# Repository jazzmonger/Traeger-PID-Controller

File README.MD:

*4/15/25 - NOTE: project has been upgrade to an ESP32S3. Touch and display are just too much for the little D1. S3 handles it no problem.  New design files now uploaded to rev 2.2.0*

This project is for a generic ESP32 Based Traeger Pellet Smoker/Grill controller that can be used on any smoker/grill that has an auger, hotrod and fan used for control. Full Home Assistant control completes it and the sky is the limit on what can be done with it using automations.  See my ESPHome Forums post for discussions https://community.home-assistant.io/t/generic-traeger-smoker-grill-controller/867494

The inspiration for much of this project came from the excellent work done be @Nebhead and the PiSmoker project (https://github.com/nebhead/PiFire) based on the Raspberry Pi. Their Discord channel is here https://discord.com/channels/1027346882156052550/1027348991135985796

While I respect the platform for what it is, I'm not a huge Raspberry Pi fan and I wanted something based on an ESP32 and ESPHome that would integrate seamlessly into Home Assistant. So, this project was born.

Some key attributes of this scaled down version:

* its written in ESPHome, so its easy to understand and modify
* It can be used standalone or with Home Assistant
* it integrates seamlessly with Home Assistant and all functions are controllable via a LoveLace dashboard both on a PC and in the Home Assistant app.
* it emulates the existing new Trager controllers in all functions and adds several new functions
* it controls 1 auger, 1 hotrod & 1 fan found on the vast majority of pellet smokers
* it uses solid state relays for control
* it uses the existing PT1000 temperature sensor (can be adapted to a PT100)
* it adds a Smith-Predicting, PID temperature compensating control
* it controls the chamber temperature within approximately +/- 5F vs the +/- 25F for existing controllers
* rotary encoder support so you can control your grill temp with a spinny knob
* it has an interactive, touch screen ili9341 display
* it adds 3 optional configurable wired meat probes
* it allows dynamic configuration of ALL paramaters so it is infinitly tuneable to any pellet smoker
* it also allows for both touch screen control of all functions as well as optional individual buttons for control.
* it adds an optional VL53L0X Time of Flight (TOF) Sensor sensor to measure hopper pellet levels
* Circuit board for this scaled down version is exactly the same size as the Traeger controller allowing easy retrofit installation.

Outstanding temperature control even when opening the lid of the smoker.  Very little overshoot when adjusting temperatures (Smith Predictor).
Fully adjustable PID Params (advanced)
Lovelace Dashboards with animated icons for fans, auger & hotrod

Full architecture doc here https://github.com/jazzmonger/Traeger-PID-Controller/blob/main/doc/1Traeger-S3-operation-summary.md

This is a work in progress. I'm not affilaiated with Traeger or any other BBQ or smoker company. The design may or may not work with your gril, so, your mileage may vary. The chip Im using in this design is an ESP32 D1 Mini. Its small size,wide availability, and versatility makes it ideal for this use. You can probably use any ESP32 based dev board, but I cannot guarantee it will work. My larger project uses an ESP32-S3 as I needed every single available GPIO on that chip, and then some. Plus I needed to use the ESP-IDF framework for that project and also needed PSRAM, hence the S3 based board choice.

This project has been a ton of fun.  It's a couple thousand lines of ESPHome code so it's not a "beginner" project by any definition.  But if you study the code long enough, you'll begin to make sense of it all - that's what I love about ESPHome. It's easily approachable by novice users. 

Also, because this controller offers the ability to completely customize literally everything, it will take time for you to realize its full potential.  The PID tuning is especially complex, but after many days of testing, I've settled on PID value parameters that do a reasonable job of keeping the chamber temps within +/- 5F or so,  a far cry from the +/-25F of the current controllers. Adding the Smith Predictor to the PID controller eliminates overshoots from wide temperature changes. Many kudos must go to @dogtreatfairy for many hours spent helping me tune the PID controller.

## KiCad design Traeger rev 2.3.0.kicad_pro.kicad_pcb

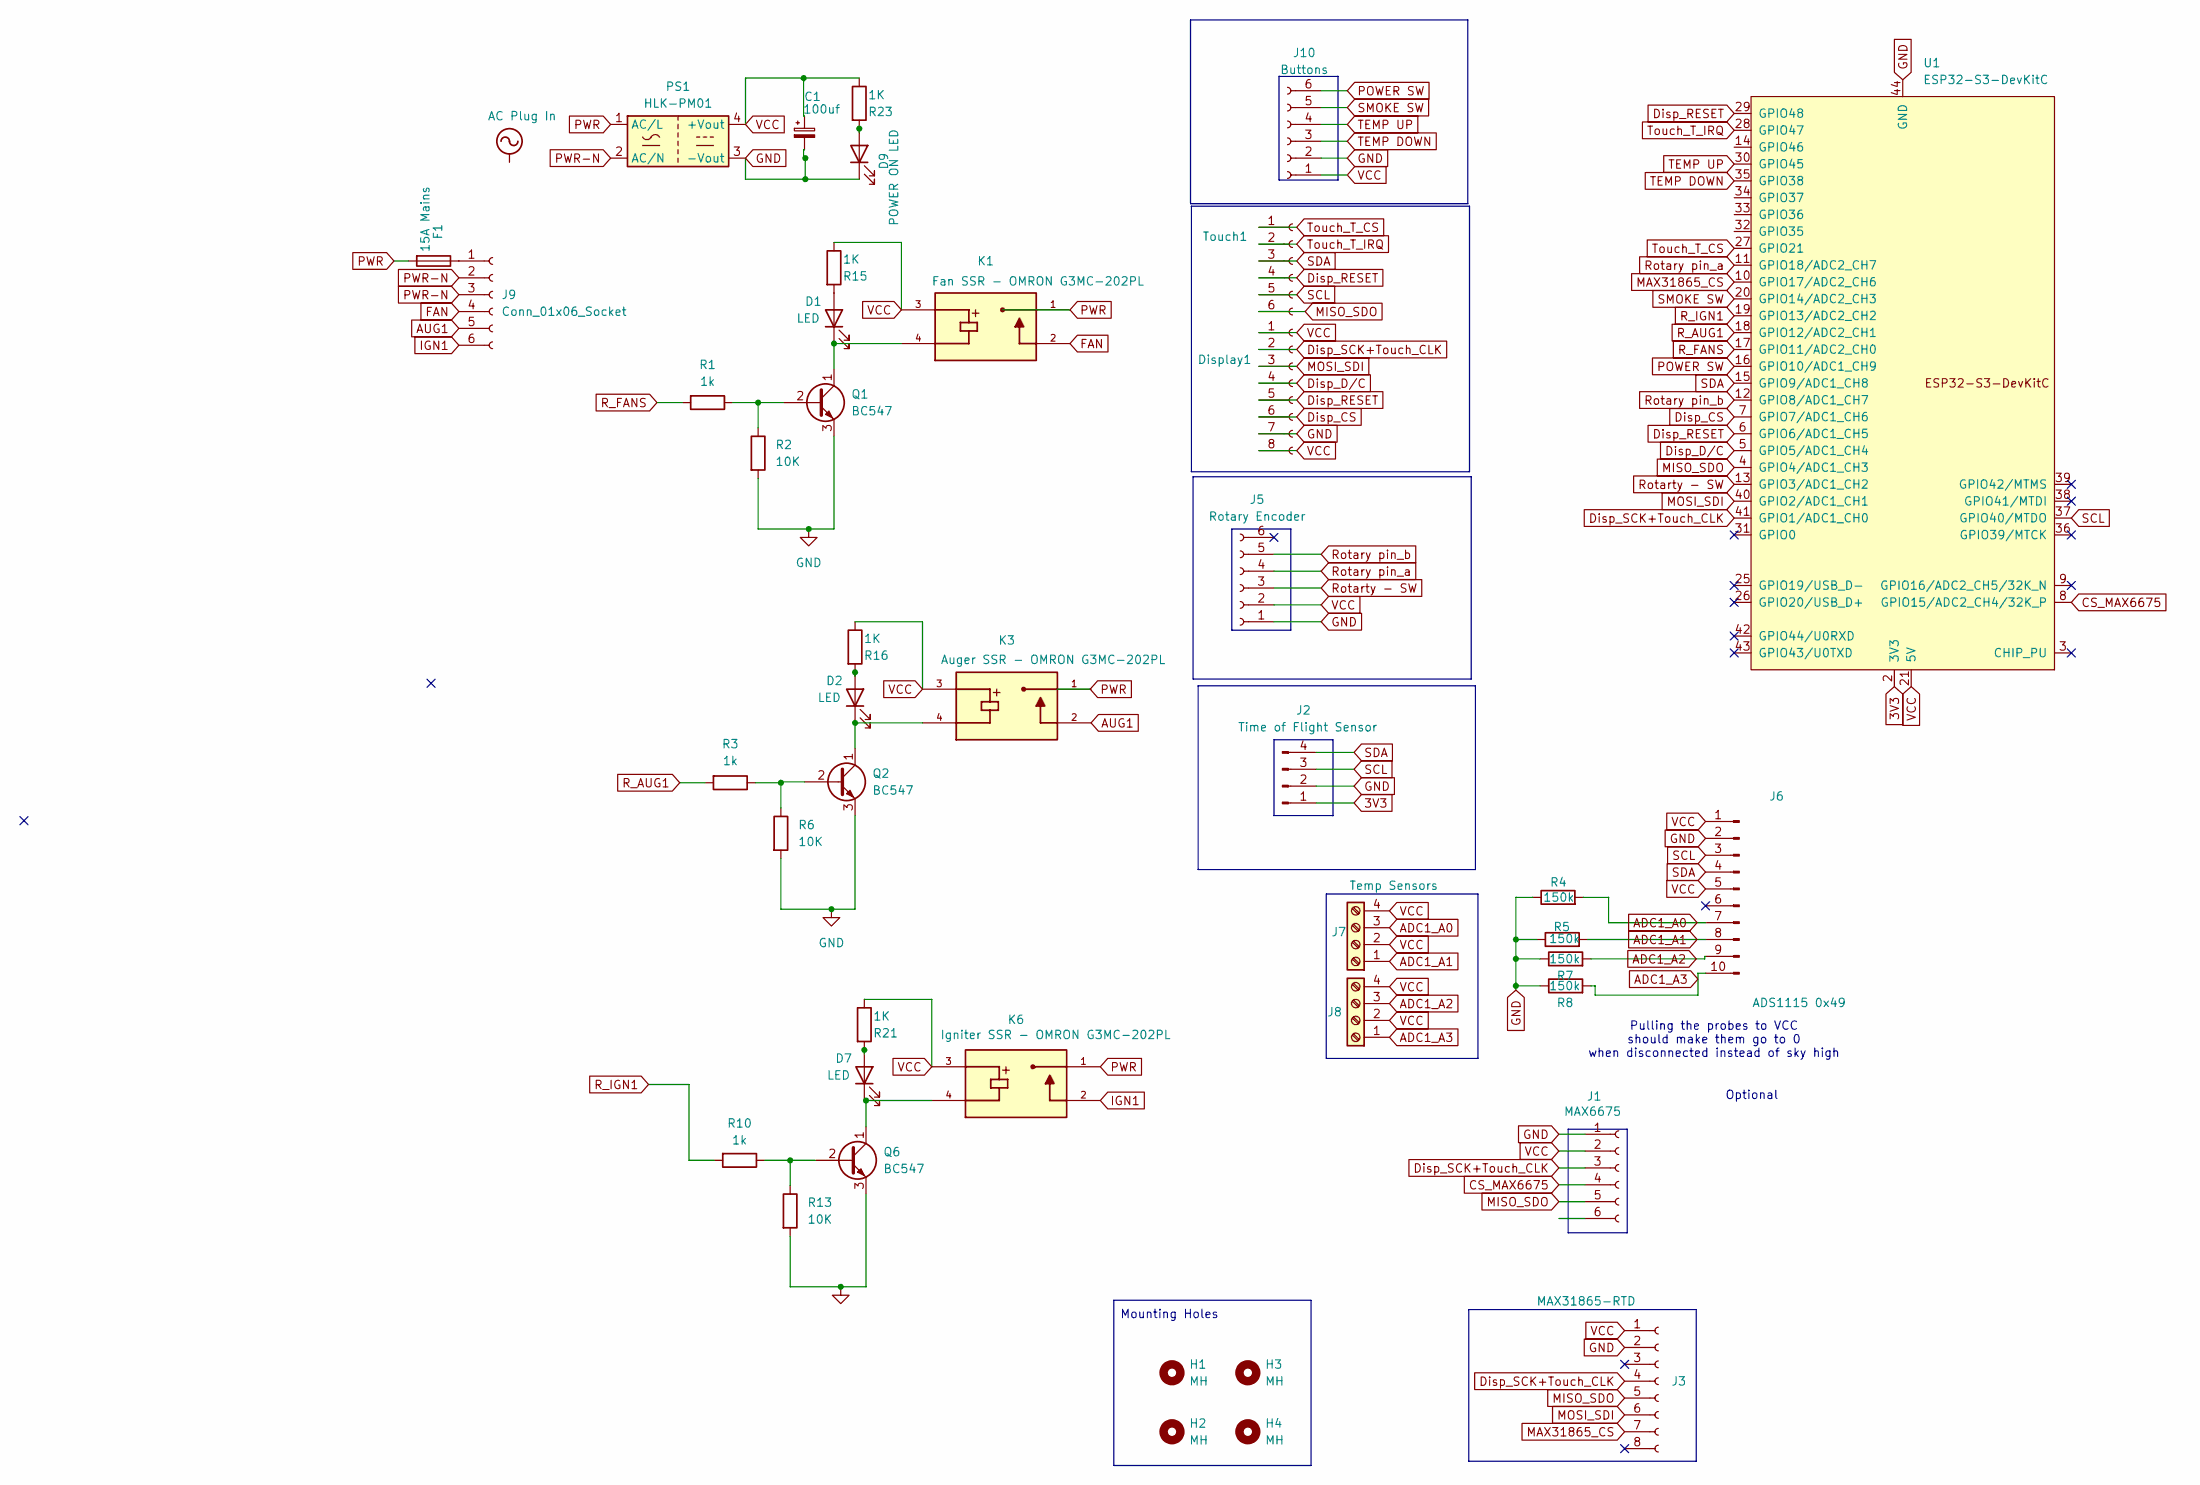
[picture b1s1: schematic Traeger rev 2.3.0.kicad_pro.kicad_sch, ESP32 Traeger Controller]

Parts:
C1: 100uf; CP_Radial_D8.0mm_P3.50mm
D1, D2, D7: LED; LED_D3.0mm
D9: POWER ON LED; LED_D3.0mm
Display1: Conn_01x08_Socket; JST_EH_B8B-EH-A_1x08_P2.50mm_Vertical
F1: 15A Mains; Fuse Block 3544-2_KEYSTONE
H1, H2, H3, H4: MH; MountingHole_3.2mm_M3
J1: MAX6675; JST_XH_B6B-XH-A_1x06_P2.50mm_Vertical
J2: Time of Flight Sensor; JST_EH_B4B-EH-A_1x04_P2.50mm_Vertical
J3: MAX31865-RTD; PinSocket_1x08_P2.54mm_Vertical
J5: Rotary Encoder; JST_XH_B6B-XH-A_1x06_P2.50mm_Vertical
J6: ADS1115 0x49; PinSocket_1x10_P2.54mm_Vertical
J7, J8: Temp Sensors; TerminalBlock_RND_205-00014_1x04_P5.00mm_Horizontal
J9: Conn_01x06_Socket; TerminalBlock_RND_205-00005_1x06_P5.00mm_Horizontal
J10: Buttons; JST_XH_B6B-XH-A_1x06_P2.50mm_Vertical
K1: Fan SSR - OMRON G3MC-202PL; RELAY_G3MB-202PDC5; PARTREV J091-E1-1A
K3: Auger SSR - OMRON G3MC-202PL; RELAY_G3MB-202PDC5; PARTREV J091-E1-1A
K6: Igniter SSR - OMRON G3MC-202PL; RELAY_G3MB-202PDC5; PARTREV J091-E1-1A
PS1: HLK-PM01; Converter_ACDC_Hi-Link_HLK-PMxx
Q1, Q2, Q6: BC547; TO-92L_Inline
R1, R3, R10: 1k; R_Axial_DIN0207_L6.3mm_D2.5mm_P7.62mm_Horizontal
R2, R6, R13: 10K; R_Axial_DIN0207_L6.3mm_D2.5mm_P7.62mm_Horizontal
R4, R5, R7, R8: 150k; R_Axial_DIN0207_L6.3mm_D2.5mm_P7.62mm_Horizontal
R15, R16, R21, R23: 1K; R_Axial_DIN0207_L6.3mm_D2.5mm_P7.62mm_Horizontal
Touch1: Conn_01x06_Socket; JST_EH_B6B-EH-A_1x06_P2.50mm_Vertical
U1: ESP32-S3-DevKitC

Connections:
3V3: J2.1, U1.1 (3V3), U1.2 (3V3)
ADC1_A0: J6.7, J7.3, R4.2
ADC1_A1: J6.8, J7.1, R5.2
ADC1_A2: J6.9, J8.3, R7.2
ADC1_A3: J6.10, J8.1, R8.2
AUG1: J9.5, K3.2
CS_MAX6675: J1.4, U1.8 (GPIO15/ADC2_CH4/32K_P)
Disp_CS: Display1.6, U1.7 (GPIO7/ADC1_CH6)
Disp_D/C: Display1.4, U1.5 (GPIO5/ADC1_CH4)
Disp_RESET: Display1.5, Touch1.4, U1.6 (GPIO6/ADC1_CH5), U1.29 (GPIO48)
Disp_SCK+Touch_CLK: Display1.2, J1.3, J3.4, U1.41 (GPIO1/ADC1_CH0)
FAN: J9.4, K1.2
GND: C1.2, D9.1 (K), Display1.7, J1.1, J2.2, J3.2, J5.1, J6.2, J10.2, PS1.3 (-Vout), Q1.3 (E), Q2.3 (E), Q6.3 (E), R2.2, R4.1, R5.1, R6.2, R7.1, R8.1, R13.2, U1.22 (GND), U1.23 (GND), U1.24 (GND), U1.44 (GND)
IGN1: J9.6, K6.2
MAX31865_CS: J3.7, U1.10 (GPIO17/ADC2_CH6)
MISO_SDO: J1.5, J3.5, Touch1.6, U1.4 (GPIO4/ADC1_CH3)
MOSI_SDI: Display1.3, J3.6, U1.40 (GPIO2/ADC1_CH1)
unnamed: D1.2 (A), R15.2
unnamed: D1.1 (K), K1.4, Q1.1 (C)
unnamed: D2.2 (A), R16.2
unnamed: D2.1 (K), K3.4, Q2.1 (C)
unnamed: D7.2 (A), R21.2
unnamed: D7.1 (K), K6.4, Q6.1 (C)
unnamed: D9.2 (A), R23.2
unnamed: F1.1, J9.1
unnamed: Q1.2 (B), R1.1, R2.1
unnamed: Q2.2 (B), R3.1, R6.1
unnamed: Q6.2 (B), R10.1, R13.1
POWER SW: J10.6, U1.16 (GPIO10/ADC1_CH9)
PWR: F1.2, K1.1, K3.1, K6.1, PS1.1 (AC/L)
PWR-N: J9.2, J9.3, PS1.2 (AC/N)
R_AUG1: R3.2, U1.18 (GPIO12/ADC2_CH1)
R_FANS: R1.2, U1.17 (GPIO11/ADC2_CH0)
R_IGN1: R10.2, U1.19 (GPIO13/ADC2_CH2)
Rotarty - SW: J5.3, U1.13 (GPIO3/ADC1_CH2)
Rotary pin_a: J5.4, U1.11 (GPIO18/ADC2_CH7)
Rotary pin_b: J5.5, U1.12 (GPIO8/ADC1_CH7)
SCL: J2.3, J6.3, Touch1.5, U1.37 (GPIO40/MTDO)
SDA: J2.4, J6.4, Touch1.3, U1.15 (GPIO9/ADC1_CH8)
SMOKE SW: J10.5, U1.20 (GPIO14/ADC2_CH3)
TEMP DOWN: J10.3, U1.35 (GPIO38)
TEMP UP: J10.4, U1.30 (GPIO45)
Touch_T_CS: Touch1.1, U1.27 (GPIO21)
Touch_T_IRQ: Touch1.2, U1.28 (GPIO47)
VCC: C1.1, Display1.1, Display1.8, J1.2, J3.1, J5.2, J6.1, J6.5, J7.2, J7.4, J8.2, J8.4, J10.1, K1.3, K3.3, K6.3, PS1.4 (+Vout), R15.1, R16.1, R21.1, R23.1, U1.21 (5V)

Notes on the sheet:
Pulling the probes to VCC should make them go to 0 when disconnected instead of sky high
Optional
Mounting Holes

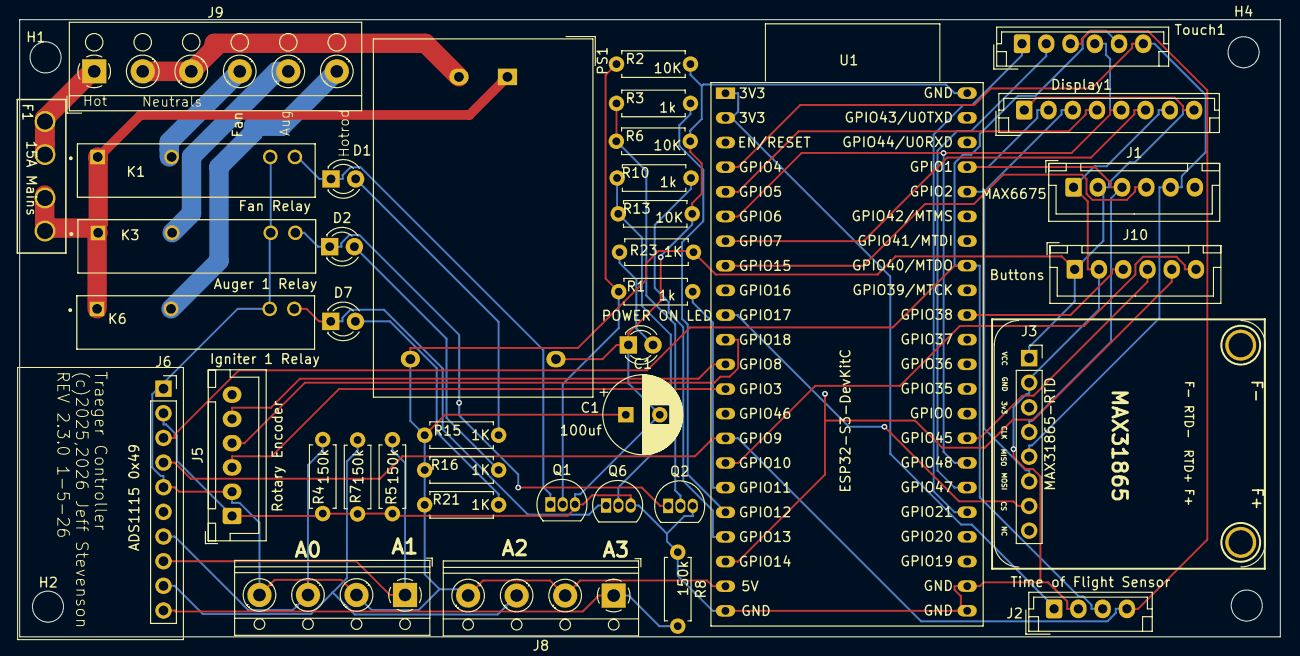
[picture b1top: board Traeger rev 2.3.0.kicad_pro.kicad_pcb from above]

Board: 2 copper layers, 129.9 x 63.6 mm, 45 parts (0 on the bottom side), 45 nets.

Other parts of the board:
U$18, U$19: MOUNTINGHOLE2.5; MOUNTINGHOLE_2.5_PLATED

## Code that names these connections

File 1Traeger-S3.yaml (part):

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
spi:
  - id: spi_bus
    clk_pin: GPIO1 #display SCK/touch T_CLK
    mosi_pin: GPIO2 #SDI-max / display /touch T_DIN
    miso_pin: GPIO4 #SDO-max / touch T_DO, display doesnt need MISO

display:
  - id: mydisplay
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    spi_id: spi_bus
    data_rate: 20MHz
    model: ILI9341 #TFT 2.4
    dc_pin: GPIO5
    cs_pin: GPIO7
    reset_pin: GPIO6
    color_palette: 8BIT
    #LED - jumper to VCC so it is always on
    rotation: 0
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          }
i2c: 
  - id:  i2c_bus
    sda: GPIO9
    scl: GPIO40
    scan: true
    timeout: 100ms
    frequency: 50kHz
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      return 0.0;
  - platform: max6675
    id: firepot_temperature_c
    cs_pin: GPIO15
    update_interval: 5s

  - platform: template
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  - platform: max31865
    #name: "RTD Temperature raw"
    id: rtd_temperature_c
    cs_pin: GPIO17 
    spi_id: spi_bus 
    reference_resistance: "4280 Ω"
    rtd_nominal_resistance: "1000 Ω"
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  - platform: rotary_encoder
    name: "Rotary Encoder"
    pin_a: 
      number: GPIO18 
      inverted: true
    pin_b: 
      number: GPIO8 
      inverted: false
    id: rotary
    on_clockwise:
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            - script.execute: sc_pot_heating
#      
  - platform: gpio
    pin: GPIO11
    name: "-Fans On/Off"
    inverted: no
    id: fans_on_off_sw
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                      id(fans_on_off_sw)->publish_state(false);

  - platform: gpio
    pin: GPIO12
    name: "-Auger 1 SW"
    inverted: no
    id: auger_1_sw
    restore_mode: ALWAYS_OFF

  - platform: gpio
    pin: GPIO13
    name: "-HotRod 1 SW"
    inverted: no
    id: hotrod_1_sw
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
  - platform: gpio
    pin:
      number: GPIO10
      mode:
        input: true
    name: "Power Button"
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
  - platform: gpio
    pin:
      number: GPIO14
      mode:
        input: true
    name: "Smoke Mode Button"
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
  - platform: gpio
    pin:
      number: GPIO38
      mode:
        input: true
    name: "Temperature Down"
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
  - platform: gpio
    pin:
      number: GPIO45
      mode:
        input: true
    name: "Temperature Up"
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
  - platform: gpio
    pin: 
      number: GPIO3
      mode:
        input: true
        pullup: true
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
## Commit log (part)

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2025-03-22 ESPHome firmware file
2025-03-22 KiCad files
2025-03-22 ESPHome firmware
2025-10-30 Create Trager BBQ KiCad files
2026-01-08 touchscreen config info
2026-01-26 Final working circuit board v 2.3.0
2026-03-25 New ESPhome config file using ESP32S3 chip

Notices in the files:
Traeger rev 2.3.0.kicad_pro.kicad_pcb:
(c) 2025, 2026 Jeff Stevenson
